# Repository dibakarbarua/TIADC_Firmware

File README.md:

TIADC-2012-13
=============

Road Accident Prevention Unit Multi Sensing-Actuation System for TIADC-2012/13. All India Third Prize Winner. C on the ARM Cortex M3 using TI's StellarisWare API

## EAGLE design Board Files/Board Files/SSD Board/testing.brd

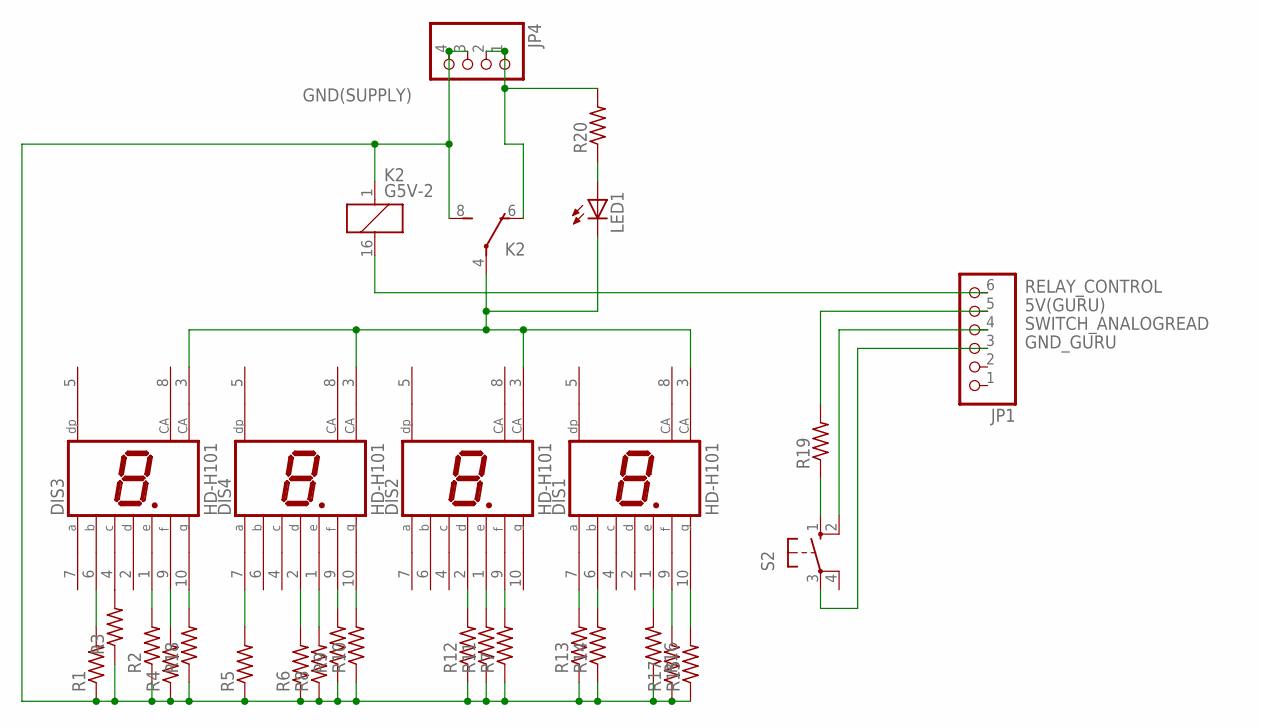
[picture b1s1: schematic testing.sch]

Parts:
DIS1, DIS2, DIS3, DIS4: HD-H101; HDSP-M
JP1: PINHD-1X6/90; 1X06/90
JP4: PINHD-1X4; 1X04
K2: G5V-2
LED1: LED5MM
R1, R2, R3, R4, R5, R6, R7, R8, R9, R10, R11, R12, R13, R14, R15, R16, R17, R18, R19, R20: RESISTOR0207/10; 0207/10
S2: 10-XX; B3F-10XX

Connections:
5V(GURU): JP1.5, R19.2
5V(SUPPLY): JP4.1, JP4.2, K2.6 (O), R20.2
GND(SUPPLY): JP4.3, JP4.4, K2.1, K2.8 (S), R1.1, R2.1, R3.1, R4.1, R5.1, R6.1, R7.1, R8.1, R9.1, R10.1, R11.1, R12.1, R13.1, R14.1, R15.1, R16.1, R17.1, R18.1
GND_GURU: JP1.3, S2.3
unnamed: DIS1.3 (CA), DIS2.3 (CA), DIS3.3 (CA), DIS4.3 (CA), K2.4, LED1.K (C)
unnamed: R19.1, S2.1 (S)
unnamed: LED1.A, R20.1
unnamed: DIS4.7 (A), R5.2
unnamed: DIS4.2 (D), R6.2
unnamed: DIS4.1 (E), R8.2
unnamed: DIS3.6 (B), R1.2
unnamed: DIS3.1 (E), R2.2
unnamed: DIS3.4 (C), R3.2
unnamed: DIS3.9 (F), R4.2
unnamed: DIS3.10 (G), R18.2
unnamed: DIS4.9 (F), R9.2
unnamed: DIS4.10 (G), R10.2
unnamed: DIS2.2 (D), R12.2
unnamed: DIS2.1 (E), R11.2
unnamed: DIS2.9 (F), R7.2
unnamed: DIS1.7 (A), R13.2
unnamed: DIS1.6 (B), R14.2
unnamed: DIS1.10 (G), R15.2
unnamed: DIS1.9 (F), R17.2
unnamed: DIS1.1 (E), R16.2
RELAY_CONTROL: JP1.6, K2.16 (2)
SWITCH_ANALOGREAD: JP1.4, S2.2 (S1)

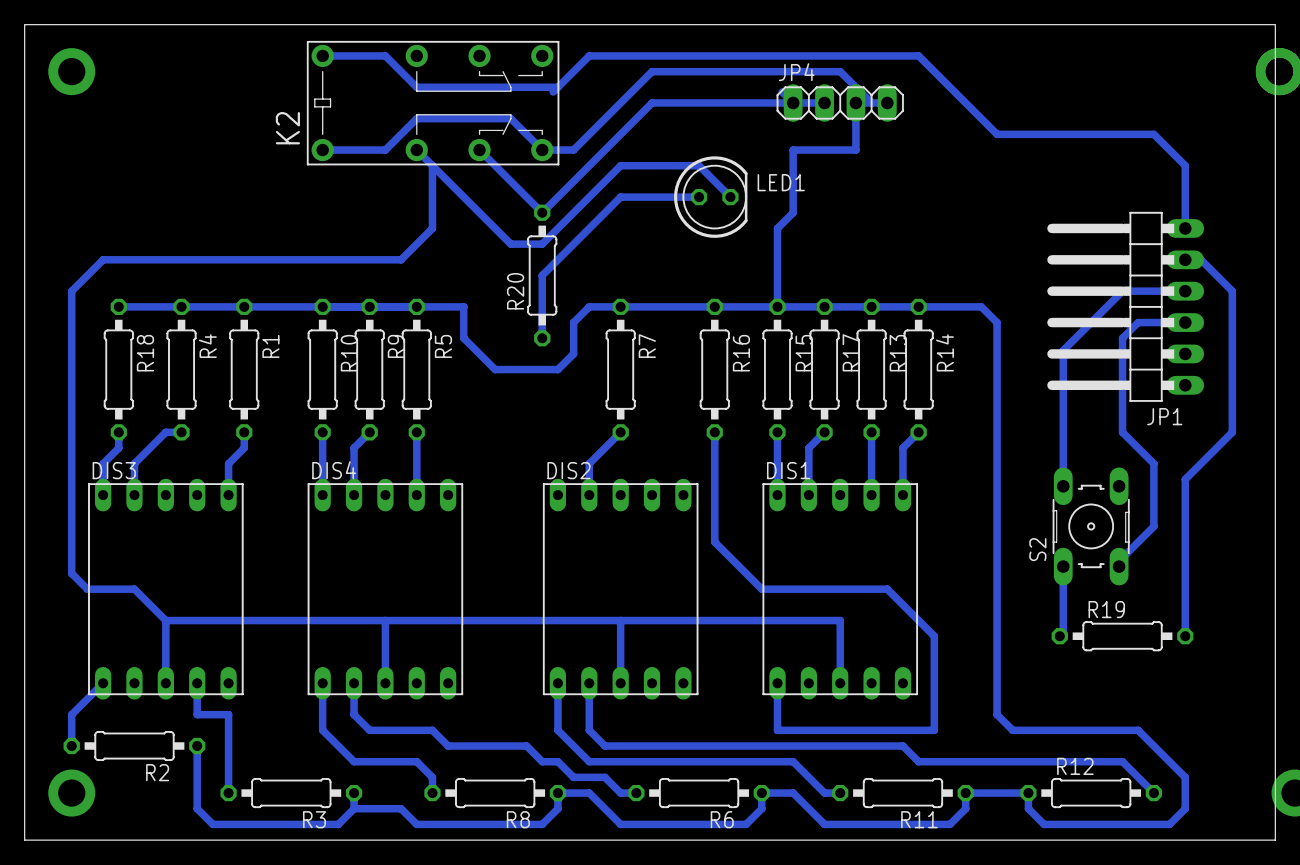
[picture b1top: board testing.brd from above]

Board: 2 copper layers, 101.3 x 66.0 mm, 29 parts (0 on the bottom side), 27 nets.

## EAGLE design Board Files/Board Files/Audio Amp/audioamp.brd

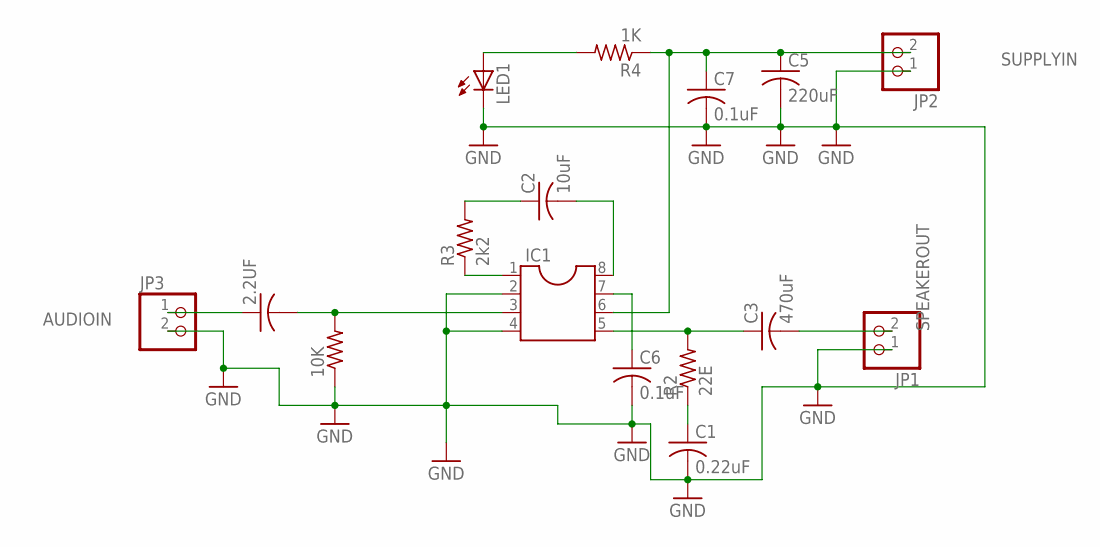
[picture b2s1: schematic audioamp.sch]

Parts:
2.2UF: C-US025-030X050; C025-030X050
10K: R-US_0207/10; 0207/10
C1: 0.22uF; C025-030X050
C2: 10uF; C025-030X050
C3: 470uF; C025-030X050
C5: 220uF; C025-030X050
C6, C7: 0.1uF; C025-030X050
IC1: DIL8; DIL08
JP1, JP2, JP3: PINHD-1X2; 1X02
LED1: LED5MM
R2: 22E; 0207/10
R3: 2k2; 0207/10
R4: 1K; 0207/10

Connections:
AUDIOIN: 2.2UF.1, JP3.1
GND: 10K.1, C1.2, C5.2, C6.2, C7.2, IC1.2, IC1.4, JP1.1, JP2.1, JP3.2, LED1.K (C)
unnamed: C2.1, R3.2
unnamed: IC1.1, R3.1
unnamed: C2.2, IC1.8
unnamed: C3.1, IC1.5, R2.2
unnamed: C1.1, R2.1
unnamed: C6.1, IC1.7
unnamed: 2.2UF.2, 10K.2, IC1.3
unnamed: LED1.A, R4.2
SPEAKEROUT: C3.2, JP1.2
SUPPLYIN: C5.1, C7.1, IC1.6, JP2.2, R4.1

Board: 2 copper layers, 16 parts (0 on the bottom side), 12 nets, no tracks yet.

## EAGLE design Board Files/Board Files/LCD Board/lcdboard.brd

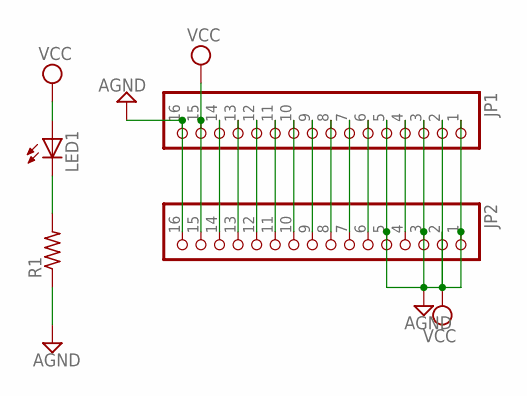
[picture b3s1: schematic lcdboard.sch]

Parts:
JP1, JP2: PINHD-1X16/90; 1X16/90
LED1: LED_ELD260; LED_LD260
R1: R-US_0204/7; 0204/7

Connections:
AGND: JP1.1, JP1.3, JP1.5, JP1.16, JP2.1, JP2.3, JP2.5, JP2.16, R1.1
unnamed: LED1.K (C), R1.2
unnamed: JP1.14, JP2.14
unnamed: JP1.13, JP2.13
unnamed: JP1.12, JP2.12
unnamed: JP1.11, JP2.11
unnamed: JP1.10, JP2.10
unnamed: JP1.9, JP2.9
unnamed: JP1.8, JP2.8
unnamed: JP1.7, JP2.7
unnamed: JP1.6, JP2.6
unnamed: JP1.4, JP2.4
VCC: JP1.2, JP1.15, JP2.2, JP2.15, LED1.A

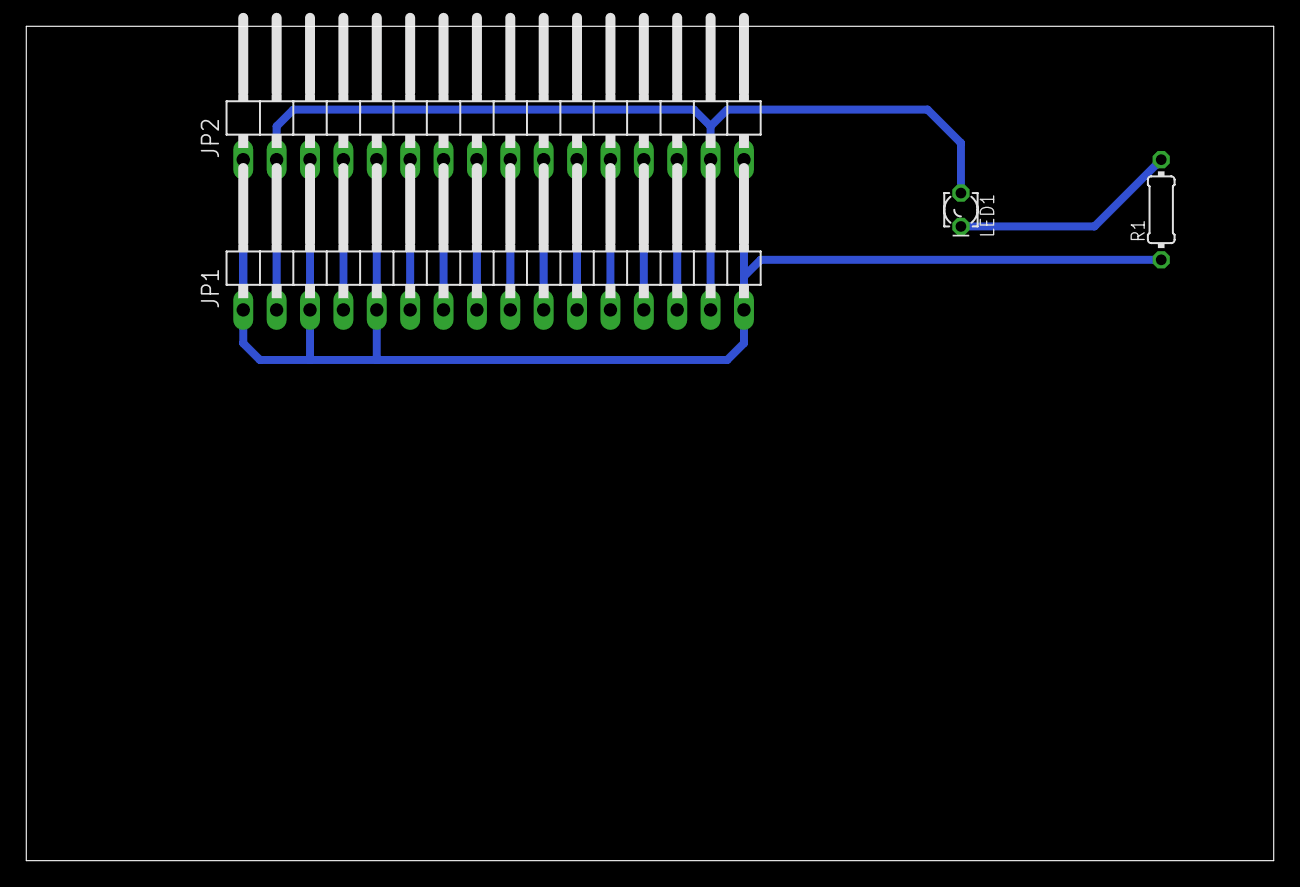
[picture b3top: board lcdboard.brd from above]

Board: 2 copper layers, 94.9 x 63.5 mm, 4 parts (0 on the bottom side), 13 nets.

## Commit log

2014-02-06 Final Commit
